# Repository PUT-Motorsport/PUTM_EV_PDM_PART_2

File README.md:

# PUTM_EV_PDM_PART_2
A pcb connecting pdm to the rest of our vehicle. ;)

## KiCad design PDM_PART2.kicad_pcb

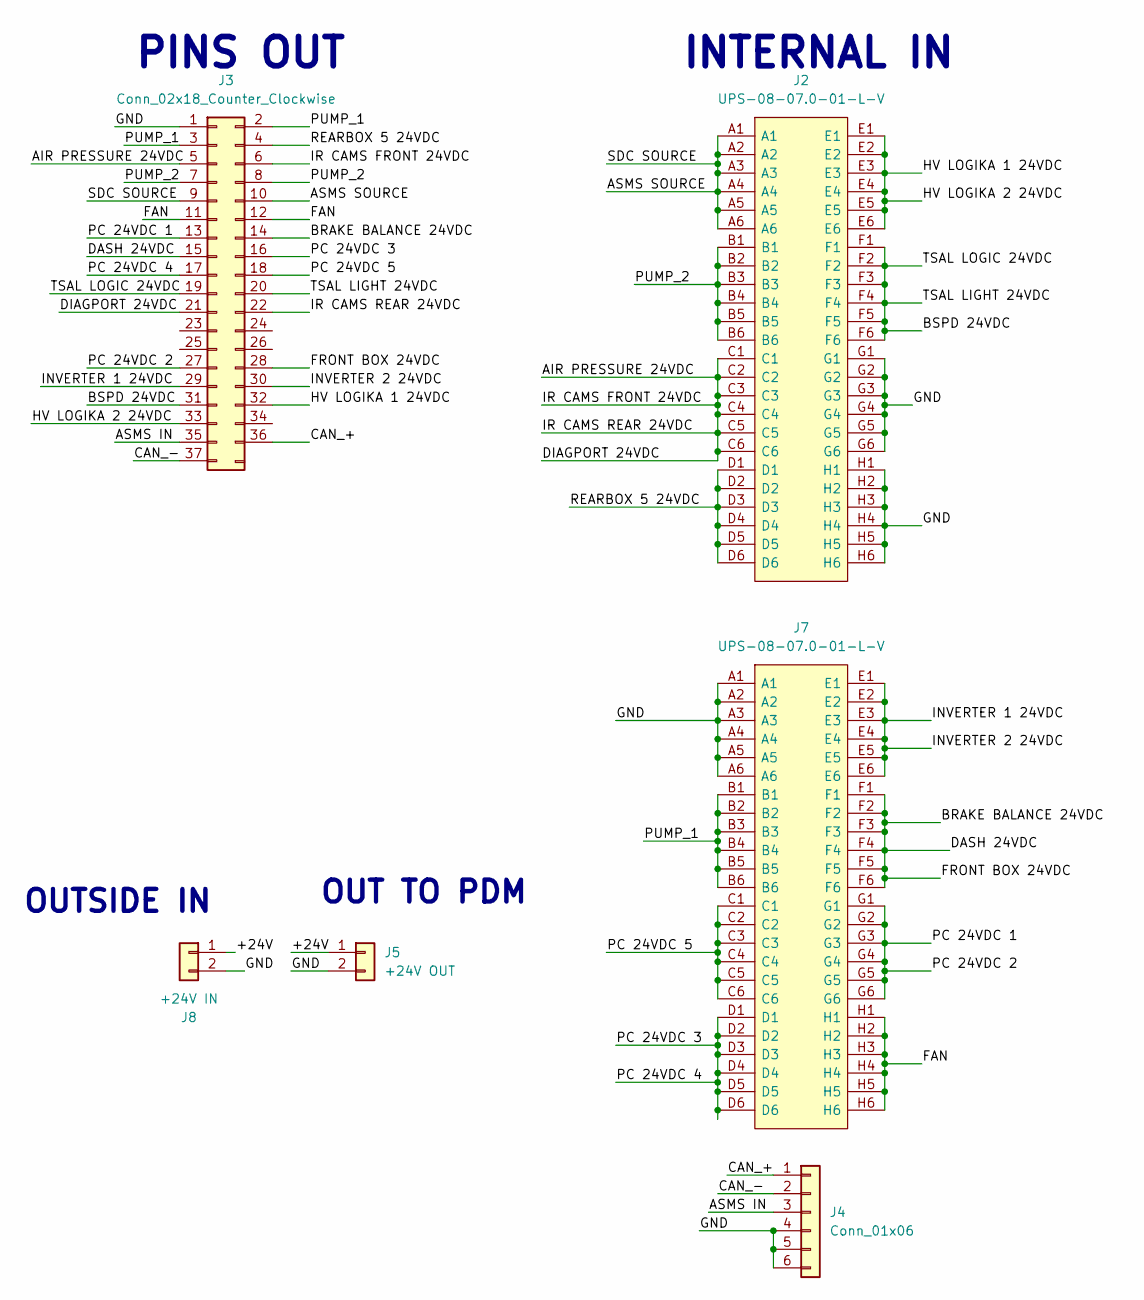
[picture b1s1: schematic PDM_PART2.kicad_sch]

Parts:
J2, J7: UPS-08-07.0-01-L-V; UPS0807001LV; Manufacturer_Part_Number UPS-08-07.0-01-L-V; Mouser Part Number 200-UPS0807.001LV
J3: Conn_02x18_Counter_Clockwise; 37 PIN DEUTSCH
J4: Conn_01x06; IDC-Header_2x03_P2.54mm_Vertical
J5: +24V OUT; SAMTEC_UPS-02-XX.X-X-X-V
J8: +24V IN; DTP104P

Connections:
/+24V: J5.1, J8.1
/AIR PRESSURE 24VDC: J2.C1, J2.C2, J2.C3, J2.C4, J2.C5, J2.C6, J3.5, J3.6, J3.21, J3.22
/ASMS IN: J3.35, J4.3
/ASMS SOURCE: J2.A1, J2.A2, J2.A3, J2.A4, J2.A5, J2.A6, J3.9, J3.10
/BRAKE BALANCE 24VDC: J3.14, J3.15, J3.28, J7.F1, J7.F2, J7.F3, J7.F4, J7.F5, J7.F6
/BSPD 24VDC: J2.F1, J2.F2, J2.F3, J2.F4, J2.F5, J2.F6, J3.19, J3.20, J3.31
/CAN_+: J3.36, J4.1
/CAN_-: J3.37, J4.2
/FAN: J3.11, J3.12, J7.H1, J7.H2, J7.H3, J7.H4, J7.H5, J7.H6
/GND: J2.G1, J2.G2, J2.G3, J2.G4, J2.G5, J2.G6, J2.H1, J2.H2, J2.H3, J2.H4, J2.H5, J2.H6, J3.1, J4.4, J4.5, J4.6, J5.2, J7.A1, J7.A2, J7.A3, J7.A4, J7.A5, J7.A6, J8.2
/HV LOGIKA 1 24VDC: J2.E1, J2.E2, J2.E3, J2.E4, J2.E5, J2.E6, J3.32, J3.33
/INVERTER 1 24VDC: J3.29, J3.30, J7.E1, J7.E2, J7.E3, J7.E4, J7.E5, J7.E6
/PC 24VDC 1: J3.13, J3.27, J7.G1, J7.G2, J7.G3, J7.G4, J7.G5, J7.G6
/PC 24VDC 3: J3.16, J3.17, J7.D1, J7.D2, J7.D3, J7.D4, J7.D5, J7.D6
/PC 24VDC 5: J3.18, J7.C1, J7.C2, J7.C3, J7.C4, J7.C5, J7.C6
/PUMP_1: J3.2, J3.3, J7.B1, J7.B2, J7.B3, J7.B4, J7.B5, J7.B6
/PUMP_2: J2.B1, J2.B2, J2.B3, J2.B4, J2.B5, J2.B6, J3.7, J3.8
/REARBOX 5 24VDC: J2.D1, J2.D2, J2.D3, J2.D4, J2.D5, J2.D6, J3.4

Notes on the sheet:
INTERNAL IN
OUTSIDE IN
OUT TO PDM
PINS OUT

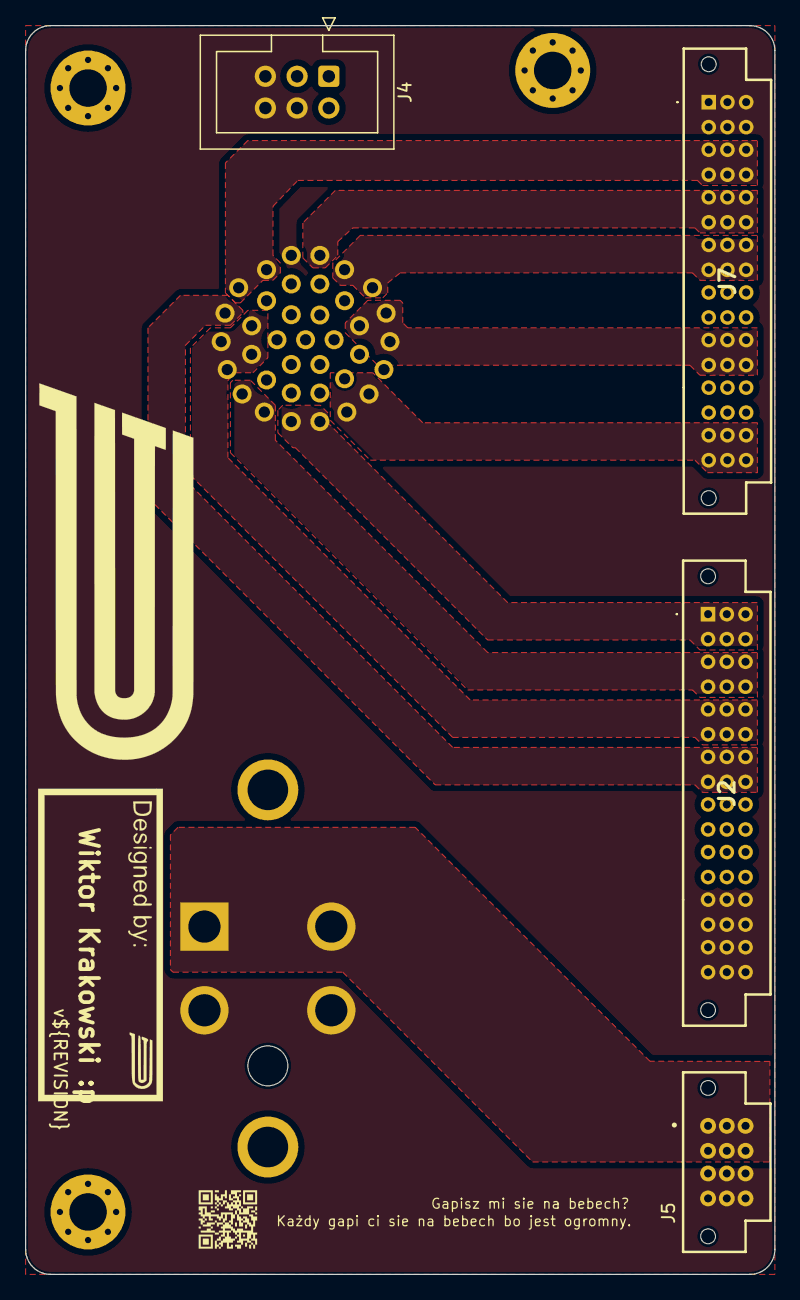
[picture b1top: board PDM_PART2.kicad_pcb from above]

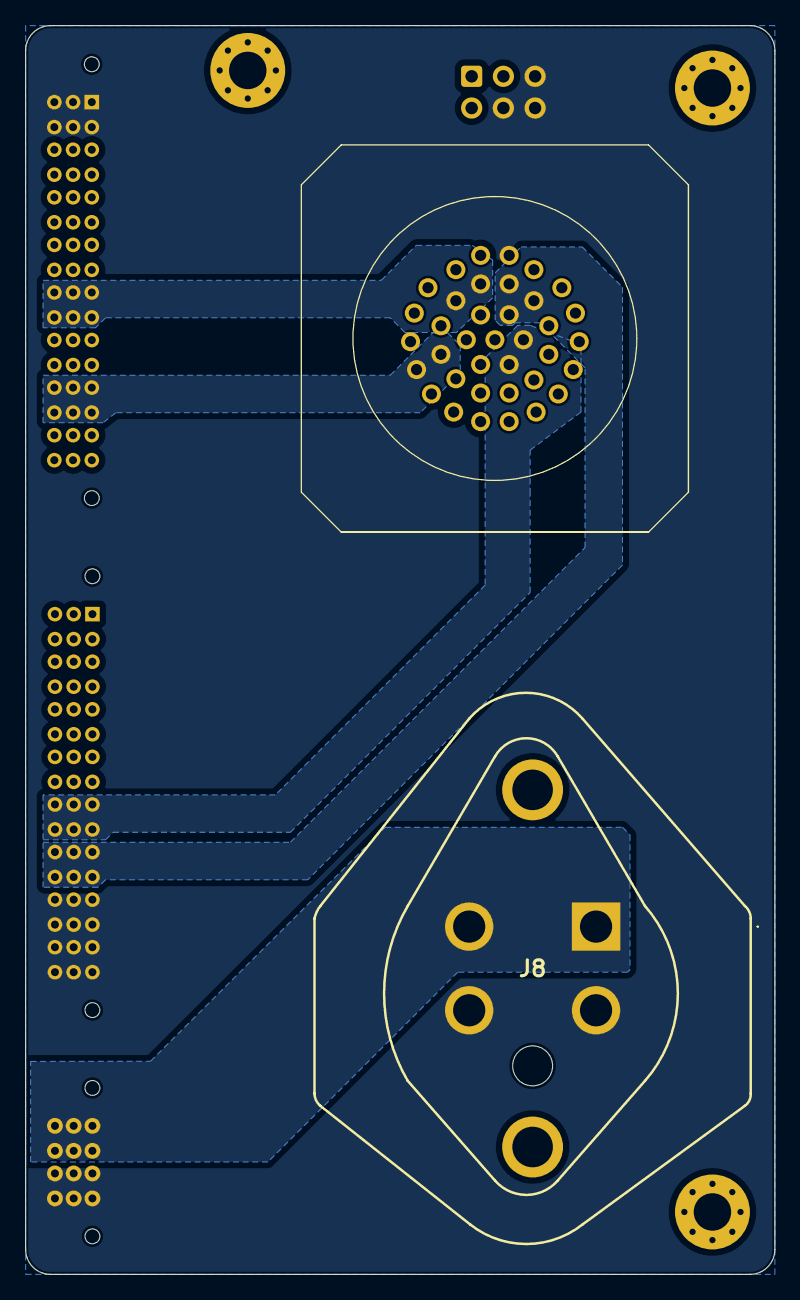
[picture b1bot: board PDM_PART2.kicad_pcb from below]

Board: 4 copper layers, 60.0 x 100.0 mm, 9 parts (2 on the bottom side), 18 nets.

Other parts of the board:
xd1, xd2, xd3: MountingHole_3mm_Pad_Via

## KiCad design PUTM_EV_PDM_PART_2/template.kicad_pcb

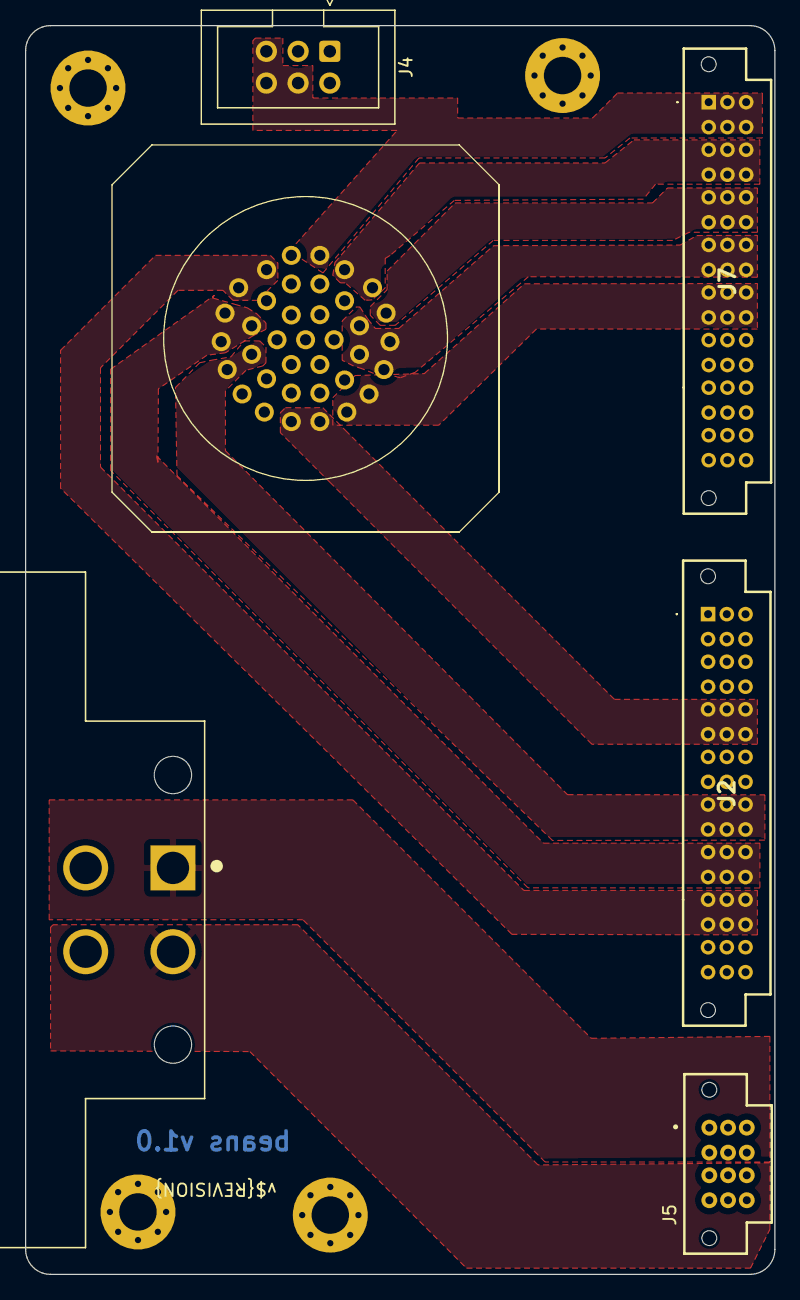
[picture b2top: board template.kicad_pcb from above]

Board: 4 copper layers, 60.0 x 100.0 mm, 10 parts (0 on the bottom side), 19 nets.

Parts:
J2, J7: UPS-08-07.0-01-L-V; UPS0807001LV
J3: Conn_02x18_Counter_Clockwise; 37 PIN DEUTSCH
J4: Conn_01x06; IDC-Header_2x03_P2.54mm_Vertical
J5: +24V OUT; SAMTEC_UPS-02-XX.X-X-X-V
J8: +24V IN; TE_DTP13-4P
xd1, xd2, xd3, xd4: MountingHole_3mm_Pad_Via

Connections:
/AIR PRESSURE 24VDC: J3.5, J3.6, J3.21, J3.22, J7.D1, J7.D2, J7.D3, J7.D4, J7.D5, J7.D6
/ASMS IN: J3.35, J4.3
/ASMS SOURCE: J2.C1, J2.C2, J2.C3, J2.C4, J2.C5, J2.C6, J3.9, J3.10
/BRAKE BALANCE 24VDC: J2.F1, J2.F2, J2.F3, J2.F4, J2.F5, J2.F6, J3.14, J3.15, J3.28
/BSPD 24VDC: J3.19, J3.20, J3.31, J7.H1, J7.H2, J7.H3, J7.H4, J7.H5, J7.H6
/CAN_H: J3.36, J4.2
/CAN_L: J3.37, J4.1
/FAN: J3.11, J7.G1, J7.G2, J7.G3, J7.G4, J7.G5, J7.G6
/GND PDM: J3.1, J4.4, J4.5, J4.6, J7.A1, J7.A2, J7.A3, J7.A4, J7.A5, J7.A6
/HV LOGIKA 1 24VDC: J2.A1, J2.A2, J2.A3, J2.A4, J2.A5, J2.A6, J3.32, J3.33
/INVERTER 1 24VDC: J2.H1, J2.H2, J2.H3, J2.H4, J2.H5, J2.H6, J3.29, J3.30
/PC 24VDC 1: J2.E1, J2.E2, J2.E3, J2.E4, J2.E5, J2.E6, J3.13, J3.27
/PC 24VDC 3: J2.G1, J2.G2, J2.G3, J2.G4, J2.G5, J2.G6, J3.16, J3.17
/PC 24VDC 5: J3.18, J7.F1, J7.F2, J7.F3, J7.F4, J7.F5, J7.F6
/PUMP_1: J3.2, J3.3, J3.25, J7.B1, J7.B2, J7.B3, J7.B4, J7.B5, J7.B6
/PUMP_2: J3.7, J3.8, J7.E1, J7.E2, J7.E3, J7.E4, J7.E5, J7.E6
/REARBOX 5 24VDC: J3.4, J7.C1, J7.C2, J7.C3, J7.C4, J7.C5, J7.C6
unnamed: J2.B1, J2.B2, J2.B3, J2.B4, J2.B5, J2.B6
unnamed: J2.D1, J2.D2, J2.D3, J2.D4, J2.D5, J2.D6

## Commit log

2024-03-20 Removed ODRIVE
    +fixed copper plates
2024-03-23 Added Fan and pump support.
2024-03-28 Add files via upload
    Fixed fan and pump routing, fixed spacing between internal connectors to fit PDM
2024-04-02 Major changes
    Changed possition of conncectors to the backside. Rerouted all connections, made universal GND
2024-04-15 Revert "Add files via upload"
    This reverts commit 9f49bbf16c7853a197d8893ae660777647b0dc2f.
2024-04-15 Ready for final review. :x
